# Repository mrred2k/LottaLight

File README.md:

# LottaLight
High Power RGB Controller with 3 Channels based on esp8266 for esphome and homeassistant

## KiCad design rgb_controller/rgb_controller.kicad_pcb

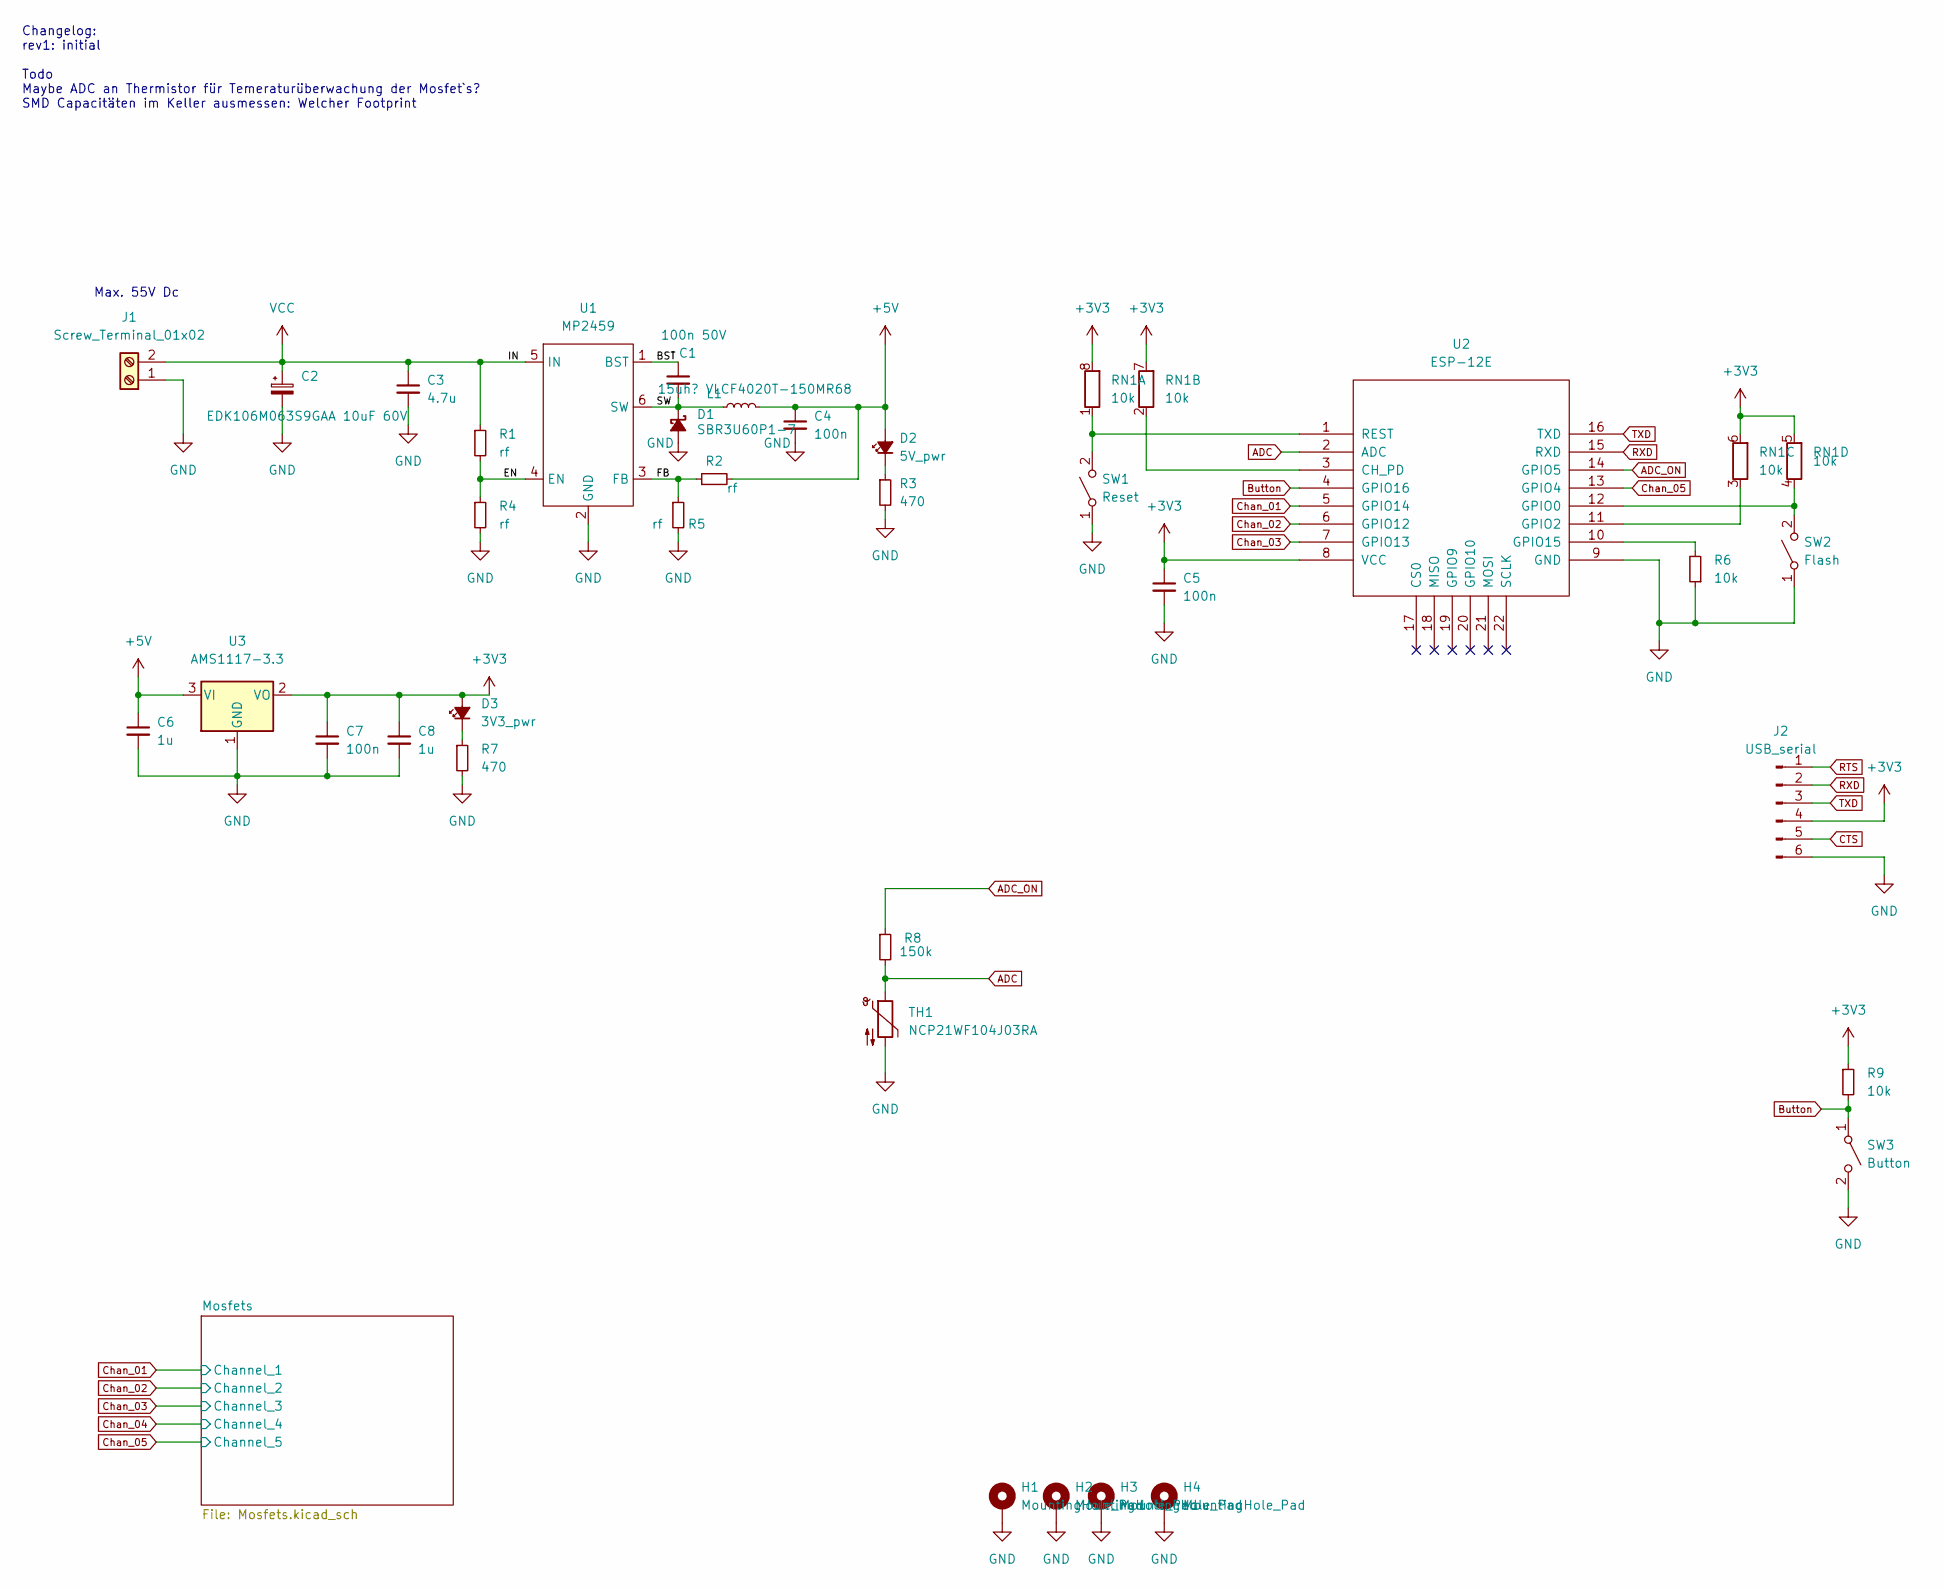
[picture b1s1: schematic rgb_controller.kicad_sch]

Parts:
C1: 100n 50V; C_0805_2012Metric
C2: EDK106M063S9GAA 10uF 60V; CP_Elec_6.3x5.7
C3: 4.7u; C_0805_2012Metric
C4, C5, C7: 100n; C_0805_2012Metric
C6, C8: 1u; C_0805_2012Metric
D1: SBR3U60P1-7; D_PowerDI-123
D2: 5V_pwr; LED_0805_2012Metric
D3: 3V3_pwr; LED_0805_2012Metric
H1, H2, H3, H4: MountingHole_Pad; MountingHole_3.2mm_M3_Pad_Via_star
J1: Screw_Terminal_01x02; TerminalBlock_Phoenix_MKDS-3-2-5.08_1x02_P5.08mm_Horizontal
J2: USB_serial; Pin_Header_Straight_1x06_smaller
L1: 15uh? VLCF4020T-150MR68; TDK_VLCF4020
R1, R2, R4, R5: rf; R_0805_2012Metric
R3, R7: 470; R_0805_2012Metric
R6, R9: 10k; R_0805_2012Metric
R8: 150k; R_0805_2012Metric
RN1: 10k; R_Array_Convex_4x0603
SW1: Reset; SW_SPST_MiniSMD
SW2: Flash; SW_SPST_MiniSMD
SW3: Button; SW_SPST_MiniSMD
TH1: NCP21WF104J03RA; R_0805_2012Metric_Pad1.20x1.40mm_HandSolder
U1: MP2459; SOT-23-6_Handsoldering
U2: ESP-12E; ESP-12E_SMD
U3: AMS1117-3.3; SOT-223-3_TabPin2

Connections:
+3V3: C5.1, C7.1, C8.1, D3.2 (A), J2.4, R9.1, RN1.5 (R4.2), RN1.6 (R3.2), RN1.7 (R2.2), RN1.8 (R1.2), U2.8 (VCC), U3.2 (VO)
+5V: C4.1, C6.1, D2.2 (A), L1.2, R2.2, U3.3 (VI)
/BST: C1.1, U1.1 (BST)
/EN: R1.2, R4.1, U1.4 (EN)
/FB: R2.1, R5.1, U1.3 (FB)
/SW: C1.2, D1.1 (K), L1.1, U1.6 (SW)
ADC: R8.2, TH1.1, U2.2 (ADC)
ADC_ON: R8.1, U2.14 (GPIO5)
Button: R9.2, SW3.1 (A), U2.4 (GPIO16)
CTS: J2.5
Chan_01: U2.5 (GPIO14); also elsewhere on the board
Chan_02: U2.6 (GPIO12); also elsewhere on the board
Chan_03: U2.7 (GPIO13); also elsewhere on the board
Chan_05: U2.13 (GPIO4); also elsewhere on the board
GND: C2.2, C3.2, C4.2, C5.2, C6.2, C7.2, C8.2, D1.2 (A), H1.1, H2.1, H3.1, H4.1, J1.1, J2.6, R3.2, R4.2, R5.2, R6.1, R7.2, SW1.1 (A), SW2.1 (A), SW3.2 (B), TH1.2, U1.2 (GND), U2.9 (GND), U3.1 (GND); also elsewhere on the board
unnamed: D2.1 (K), R3.1
unnamed: D3.1 (K), R7.1
unnamed: R6.2, U2.10 (GPIO15)
unnamed: RN1.1 (R1.1), SW1.2 (B), U2.1 (REST)
unnamed: RN1.2 (R2.1), U2.3 (CH_PD)
unnamed: RN1.3 (R3.1), U2.11 (GPIO2)
unnamed: RN1.4 (R4.1), SW2.2 (B), U2.12 (GPIO0)
RTS: J2.1
RXD: J2.2, U2.15 (RXD)
TXD: J2.3, U2.16 (TXD)
VCC: C2.1, C3.1, J1.2, R1.1, U1.5 (IN); also elsewhere on the board

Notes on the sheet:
Changelog: rev1: initial Todo Maybe ADC an Thermistor für Temeraturüberwachung der Mosfet`s? SMD Capacitäten im Keller ausmessen: Welcher Footprint
Max. 55V Dc

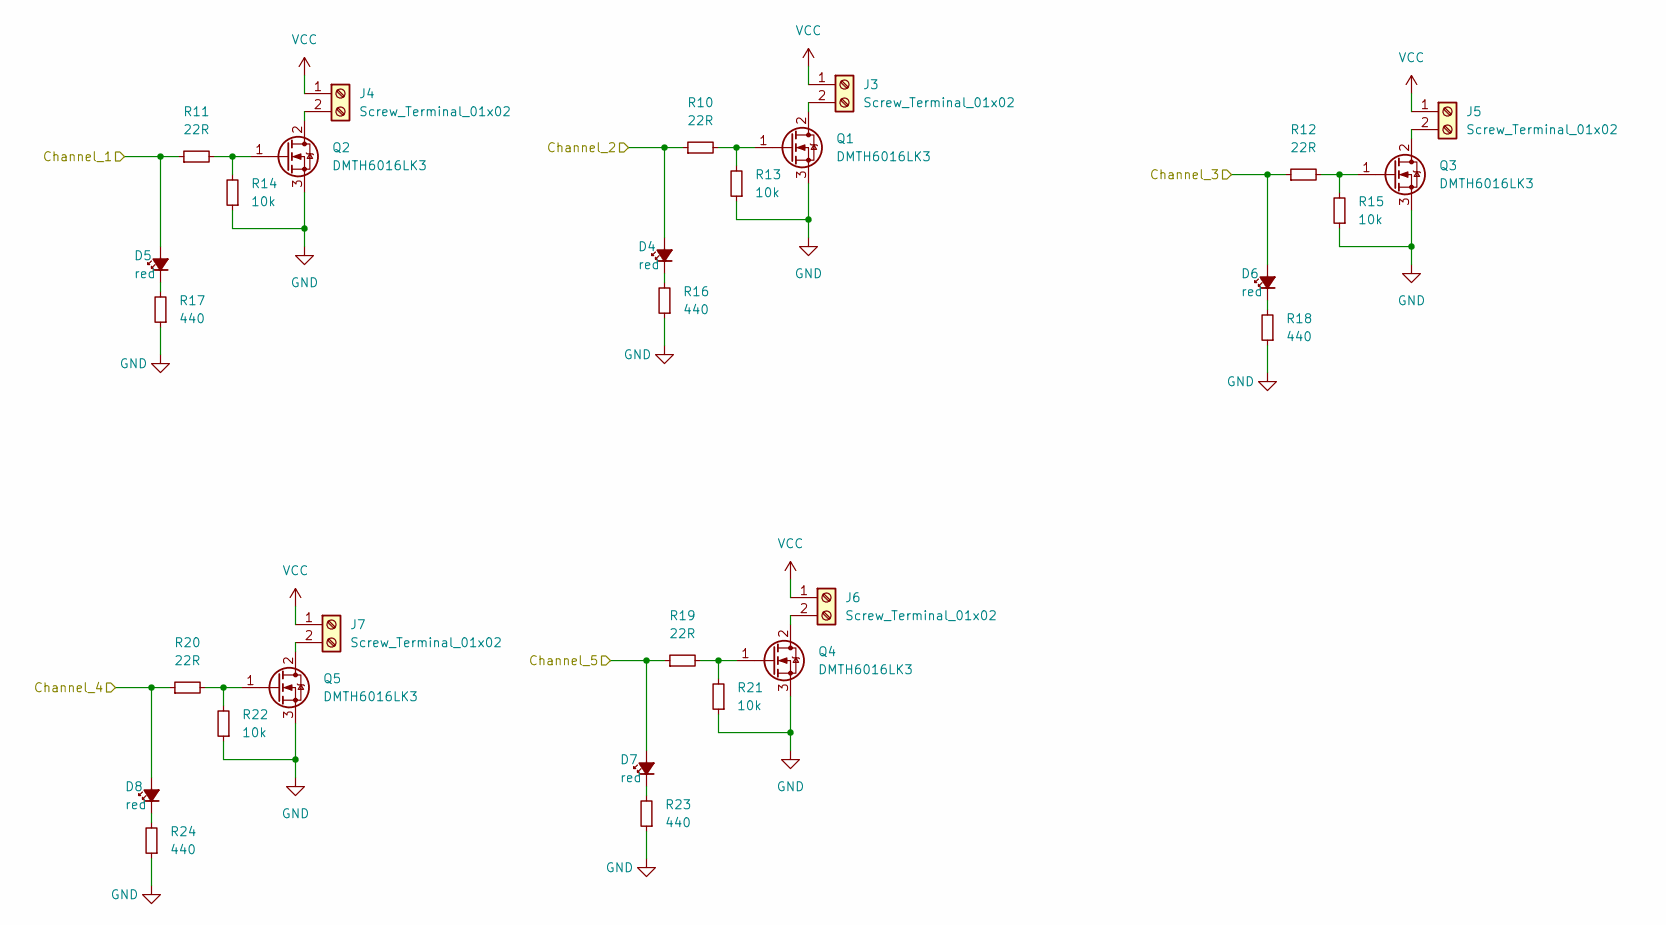
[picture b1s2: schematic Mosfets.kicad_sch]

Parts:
D4, D5, D6, D7, D8: red; LED_0805_2012Metric_Pad1.15x1.40mm_HandSolder
J3, J4, J5, J6, J7: Screw_Terminal_01x02; TerminalBlock_Phoenix_MKDS-3-2-5.08_1x02_P5.08mm_Horizontal
Q1, Q2, Q3, Q4, Q5: DMTH6016LK3; TO-263-2
R10, R11, R12, R19, R20: 22R; R_0805_2012Metric_Pad1.20x1.40mm_HandSolder
R13, R14, R15, R21, R22: 10k; R_0805_2012Metric_Pad1.20x1.40mm_HandSolder
R16, R17, R18, R23, R24: 440; R_0805_2012Metric_Pad1.20x1.40mm_HandSolder

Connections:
Chan_01: D5.2 (A), R11.1; also elsewhere on the board
Chan_02: D4.2 (A), R10.1; also elsewhere on the board
Chan_03: D6.2 (A), R12.1; also elsewhere on the board
Chan_04: D8.2 (A), R20.1
Chan_05: D7.2 (A), R19.1; also elsewhere on the board
GND: Q1.3 (S), Q2.3 (S), Q3.3 (S), Q4.3 (S), Q5.3 (S), R13.1, R14.1, R15.1, R16.1, R17.1, R18.1, R21.1, R22.1, R23.1, R24.1; also elsewhere on the board
unnamed: D4.1 (K), R16.2
unnamed: D5.1 (K), R17.2
unnamed: D6.1 (K), R18.2
unnamed: D7.1 (K), R23.2
unnamed: D8.1 (K), R24.2
unnamed: J3.2, Q1.2 (D)
unnamed: J4.2, Q2.2 (D)
unnamed: J5.2, Q3.2 (D)
unnamed: J6.2, Q4.2 (D)
unnamed: J7.2, Q5.2 (D)
unnamed: Q1.1 (G), R10.2, R13.2
unnamed: Q2.1 (G), R11.2, R14.2
unnamed: Q3.1 (G), R12.2, R15.2
unnamed: Q4.1 (G), R19.2, R21.2
unnamed: Q5.1 (G), R20.2, R22.2
VCC: J3.1, J4.1, J5.1, J6.1, J7.1; also elsewhere on the board

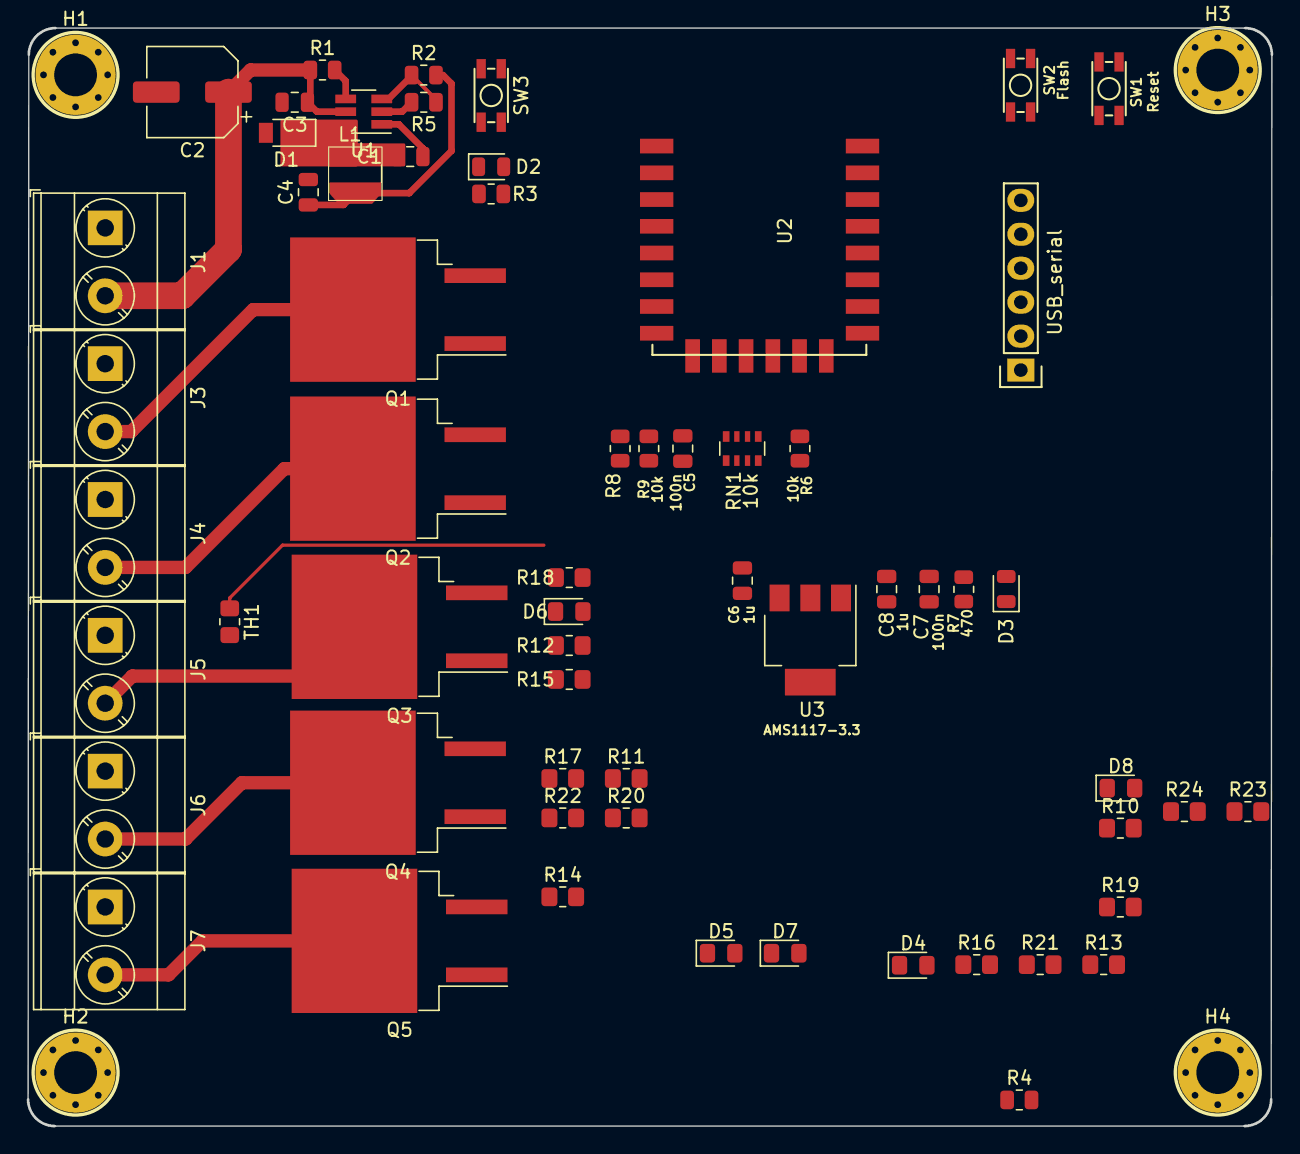
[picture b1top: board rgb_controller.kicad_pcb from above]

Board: 2 copper layers, 93.1 x 82.1 mm, 65 parts (0 on the bottom side), 40 nets.

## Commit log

2023-03-23 Initial Commit
    All files from Kicad
